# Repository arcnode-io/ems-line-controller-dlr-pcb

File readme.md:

# DLR PCB 🌡️⚡

> Single-PCB CM4 carrier for a solar-powered, cellular-connected RTU — mounts to a transmission tower cross-arm, integrates SoM + cellular modem + IEEE 738 sensor suite + solar/LiFePO4 power management. Feeds [`dlr-operating-envelope`](https://gitlab.com/arcnode-io/dlr-operating-envelope).

Solar-powered remote terminal unit (RTU) deployed unattended on transmission tower cross-arms. A ~20W solar panel and ~50Wh LiFePO4 battery keep the CM4 running indefinitely with cellular PSM idle. A soldered Quectel BG770A (LTE Cat-M1) publishes sensor data and dynamic ratings to the MQTT broker — no site WiFi or wired backhaul required. The unit is designed for 30-year conductor-adjacent deployment with no scheduled maintenance.

~100x80mm 4-layer industrial carrier. Raspberry Pi CM4 (DF40 dual-connector) + Quectel BG770A LCC + FLIR Lepton 3.5 (SPI) + DHT22 (GPIO) + SI1145 (I2C) + YL-83 (analog via ADS1115). MPPT charger from PV input, LiFePO4 BMS, buck for 5V SoM rail, AP2112K LDO for 3.3V analog front-end. Conformal coated, IP55 when potted in field enclosure.

## System Context

```plantuml
rectangle transmission_tower {
  rectangle field_enclosure {
    rectangle dlr_carrier {
      rectangle cm4_som
      rectangle cellular_module
      rectangle sensors
      rectangle power_mgmt
    }
  }
  rectangle solar_panel
  rectangle lifepo4_battery
  rectangle conductor
}

queue mqtt_broker
rectangle dlr_pst_sim

solar_panel -d- power_mgmt: PV input
power_mgmt -l- lifepo4_battery: charge / discharge
power_mgmt -d- cm4_som: 5V / 3V3
conductor -u- sensors: thermal view\n(FLIR Lepton)
sensors -r- cm4_som: SPI / I2C / GPIO
cm4_som -r- cellular_module: UART + USB2
cellular_module -r- mqtt_broker: LTE Cat-M1
mqtt_broker -r- dlr_pst_sim: tap \n adjustment \n commands
```

The carrier is the physical sensing + edge-compute layer of the DLR feedback loop. Every measurement flows through the IEEE 738 calculation in [`dlr-operating-envelope`](https://gitlab.com/arcnode-io/dlr-operating-envelope) and ultimately determines whether the phase shift transformer adjusts its tap position.

## Board Spec

```mermaid
graph LR
    SOLAR["Solar Panel<br/>~20W 12V"] --> MPPT["MPPT Charger"]
    MPPT --> BAT["LiFePO4 4S<br/>~50Wh + BMS"]
    BAT --> BUCK["Buck<br/>5V 3A"]
    BUCK --> CM4["CM4 SoM<br/>DF40 x2"]
    BUCK --> BG["Quectel BG770A<br/>Cat-M1 LCC"]
    BUCK --> LDO["AP2112K<br/>3.3V LDO"]
    LDO --> ADC["ADS1115<br/>I2C 0x48"]
    LDO --> UV["SI1145<br/>I2C 0x60"]
    CM4 --> FLIR["FLIR Lepton 3.5<br/>SPI0 + GPIO25"]
    CM4 --> DHT["DHT22<br/>GPIO4"]
    CM4 --> ADC
    CM4 --> UV
    ADC --> RAIN["YL-83<br/>Analog 0-3.3V"]

    style SOLAR fill:#dc4,stroke:#333
    style MPPT fill:#a94,stroke:#333
    style BAT fill:#a94,stroke:#333
    style BUCK fill:#a94,stroke:#333
    style LDO fill:#a94,stroke:#333
    style CM4 fill:#4a9,stroke:#333,color:#fff
    style BG fill:#49a,stroke:#333,color:#fff
    style FLIR fill:#49a,stroke:#333,color:#fff
    style DHT fill:#94a,stroke:#333,color:#fff
    style ADC fill:#94a,stroke:#333,color:#fff
    style UV fill:#94a,stroke:#333,color:#fff
    style RAIN fill:#669,stroke:#333,color:#fff
```

## CM4 Pinout

```mermaid
flowchart LR
classDef default fill:transparent,stroke:#333
classDef pwr fill:#4a9,stroke:#333,color:#fff
classDef spi fill:#49a,stroke:#333,color:#fff
classDef i2c fill:#94a,stroke:#333,color:#fff
classDef gpio fill:#a94,stroke:#333,color:#fff
classDef uart fill:#a49,stroke:#333,color:#fff
classDef usb fill:#669,stroke:#333,color:#fff

subgraph cm4 ["CM4 (DF40-100)"]
  p_5v["5V_IN"]
  p_sda["GPIO2 SDA1"]
  p_scl["GPIO3 SCL1"]
  p_g4["GPIO4"]
  p_g25["GPIO25"]
  p_mosi["GPIO10 MOSI"]
  p_miso["GPIO9 MISO"]
  p_sck["GPIO11 SCLK"]
  p_ce0["GPIO8 CE0"]
  p_txd["GPIO14 TXD"]
  p_rxd["GPIO15 RXD"]
  p_usb["USB2 D+/D-"]
end

subgraph onboard ["Carrier Components"]
  flir["FLIR Lepton 3.5"]
  dht["DHT22"]
  si["SI1145"]
  ads["ADS1115"]
  yl["YL-83"]
  bg["BG770A"]
end

p_mosi --> flir
p_miso --> flir
p_sck --> flir
p_ce0 --> flir
p_g25 --> flir
p_g4 --> dht
p_sda --> si
p_scl --> si
p_sda --> ads
p_scl --> ads
ads --> yl
p_txd --> bg
p_rxd --> bg
p_usb --> bg

class p_5v pwr
class p_mosi,p_miso,p_sck,p_ce0 spi
class p_sda,p_scl i2c
class p_g4,p_g25 gpio
class p_txd,p_rxd uart
class p_usb usb
```

## Sensor Interfaces

| Sensor | Interface | CM4 Pins | Sample Rate | Measurement | Feeds IEEE 738 Variable |
|--------|-----------|----------|-------------|-------------|------------------------|
| FLIR Lepton 3.5 | SPI0 + VSYNC | GPIO 8, 9, 10, 11, 25 | 8.6 Hz (frame) | Conductor surface temp | $R_{thermal}$ |
| DHT22 | GPIO4 (1-Wire) | GPIO 4 | 0.5 Hz | Ambient temp + humidity | $T_{amb}$ |
| SI1145 | I2C (0x60) | GPIO 2, 3 | 10 Hz | UV / Visible / IR irradiance | $\Delta T_{solar}$ |
| YL-83 → ADS1115 | I2C (0x48) ch0 | GPIO 2, 3 | 860 SPS | Rain intensity (0–3.3V analog) | $\Delta T_{rain}$ |

Every sensor reading on this board maps to exactly one term in the IEEE 738 dynamic rating equation:

$$ I_{max} = \sqrt{\frac{q_c + q_r - q_s}{R_{ac}}} $$

## Anemometer Variants

Single PCB + single firmware binary. Variant lives in the **kit BOM** — sensor,
cable harness, PV panel, and battery differ per SKU. Both sensors speak
NMEA 0183 (`$..MWV`) over RS-485, so the firmware driver is talker-agnostic.

### Kit BOM

| Component | High-wind kit (`DLR-CRN-HW`) | Low-wind kit (`DLR-CRN-LW`) |
|-----------|------------------------------|------------------------------|
| PCB | `dlr-pcb-v1` (same) | `dlr-pcb-v1` (same) |
| Firmware | `dlr-operating-envelope` (same binary) | `dlr-operating-envelope` (same binary) |
| Sensor | Calypso ULP STD | Vaisala WMT702 |
| Sensor wire protocol | NMEA `$IIMWV` over RS-485 | NMEA `$WIMWV` over RS-485 |
| Sensor accuracy (V<2 m/s) | ±5 % + 0.2 m/s offset (1 m/s threshold) | **±0.1 m/s** (0.01 m/s threshold) |
| Sensor op temp | unspecified (consumer-grade) | -10 to +60 °C |
| Cable harness | 5 m bare-wire to M12-5P | 5 m Cannon Trident 19-way to M12-5P |
| PV panel | 20 W | **30 W** |
| Battery | 50 Wh LiFePO4 | **100 Wh LiFePO4** |
| Sticker | `HW-1.0` | `LW-1.0` |
| Kit cost (approx) | ~$650 | ~$2350 |

### When to deploy which variant

Per-site SKU pick uses NREL WIND Toolkit climatology (or customer SCADA wx
history when available). Threshold: fraction-of-year with V_w < 1 m/s
perpendicular to conductor.

| Climatology | Variant | Why |
|---|---|---|
| ≤ 15 % yr V_w < 1 m/s (ridge / coastal / open plain w/ mean ≥ 6 m/s) | high-wind | uplift slice below 1 m/s is marginal; static fallback below threshold is fine |
| > 15 % yr V_w < 1 m/s (valley / sheltered / open plain w/ mean ≤ 5 m/s) | low-wind | uplift slice is material; pay $1.7 k premium to capture it |

### Fallback policy (both variants)

When the sensor reports `void` status, times out, or has a checksum/parse
error, the driver returns `None`. The IEEE 738 layer collapses None →
`V_w = 0.0` → natural-convection-only ampacity = the conductor's static
rating. Same conservative fallback used for the icing-fallback policy.

### Variant power budget

| | High-wind | Low-wind |
|---|---|---|
| Sensor continuous draw | 1 mW | 480 mW |
| System daily energy | 29.1 Wh | 40.6 Wh |
| Winter PV harvest (worst) | 45 Wh | 67.5 Wh |
| Winter margin | 1.55× | **1.66×** |
| Battery autonomy at 0 PV | 1.58 d | **2.22 d** |

Low-wind variant's 30 W / 100 Wh upgrade absorbs the WMT702's higher draw and
restores both winter margin and 2-day autonomy.

## Power Budget

| Rail | Source | Consumer | Idle (PSM) | Typical | Peak |
|------|--------|----------|------------|---------|------|
| 5V | Buck | CM4 | 80 mA | 1400 mA | 3000 mA (boot) |
| 5V | Buck | Quectel BG770A | <1 mA | 100 mA | 250 mA (TX) |
| 5V | Buck | FLIR Lepton 3.5 | 150 mA | 150 mA | 650 mA (shutter) |
| 5V | Buck | DHT22 | 1.5 mA | 1.5 mA | 2.5 mA |
| 3.3V | AP2112K LDO | ADS1115 + SI1145 + YL-83 | 9 mA | 9 mA | 14 mA |
| | | **Total @ 5V equiv** | **240 mA** | **1660 mA** | **3920 mA** |

Daily energy with realistic CM4-always-on idle + 1/min sensor wake + 1/15 min cellular TX: **~29 Wh/day** (derived in `theory.ipynb`). A 50 Wh battery (90% DoD) gives ~1.6 days autonomy with no PV. A 20W panel at 2.5 sun-hours/day (winter Northeast US worst case) delivers ~45 Wh/day after MPPT η — **1.55x winter margin**, 2.5x annual avg.

## Environmental

| Parameter | Spec | Notes |
|-----------|------|-------|
| Operating temp | -20°C to +85°C | CM4 commercial spec; cold-start heater required below -20°C |
| Conformal coat | Dow Corning 1-2577 | Applied post-assembly, mask connectors |
| Enclosure rating | IP55 (with field enclosure) | Board alone is not rated |
| Vibration | IEC 60068-2-6 (5–500 Hz, 2g) | Transmission tower wind loading |
| Expected service life | 30 years | Matches conductor replacement cycle |
| MTBF | >200,000 hours | Derated per MIL-HDBK-217F |
| Mounting | M3 standoffs, 4-corner | Single rigid PCB — no stack |

## Fabrication Pipeline

The project fabricates **two PCBs** (per ADR-013): the main carrier and the Lepton daughterboard. Both go through the same flow.

```
 1. uv run poe notebook         → theory.ipynb: power budget + signal integrity
 2. uv run poe build            → SKiDL netlist (main carrier + daughterboard)
 3. uv run poe sim              → validate buck regulation, MPPT, I2C/SPI timing
 4. /generate-schematic         → professional .kicad_sch (each PCB)

    ┌──────────────────────────────────────────────────────┐
    │  HUMAN: open pcbnew, import netlist, save, close     │
    └──────────────────────────────────────────────────────┘

 5. /layout-pcb                 → place + autoroute + ground pour + DRC

    ┌──────────────────────────────────────────────────────┐
    │  HUMAN: review SVG, adjust pcb_placement.yaml        │
    └──────────────────────────────────────────────────────┘

 6. uv run poe validate-asm     → DRC 0 errors
 7. uv run poe generate-asm     → gerbers + BOM + CPL (per board)
```

## Layer Stack

| Layer | Use |
|-------|-----|
| F.Cu | Signal — high-speed (SPI 20MHz, USB2.0 to BG770A) |
| In1.Cu | GND pour (unbroken under FLIR + cellular module) |
| In2.Cu | Power planes — 5V, 3V3, BAT |
| B.Cu | Signal — low-speed (I2C, GPIO, UART) |

Unbroken ground plane under the Lepton is critical — SPI runs at 20 MHz and the thermal imager is noise-sensitive. USB2.0 to the BG770A is differential-routed at 90Ω matched impedance with GND directly below. Analog traces from YL-83 to ADS1115 are guard-ringed on F.Cu. Cellular antenna is 50Ω microstrip to a u.FL connector.

## Project Structure

```
├── pyproject.toml              # Dependencies and build config
├── theory.ipynb                # Power budget + signal integrity derivation
├── sim/
│   ├── model.py                # Buck regulation, LDO dropout, I2C/SPI timing
│   └── test_run.py             # Assert simulation matches theory
├── cad/
│   ├── netlist/
│   │   ├── model.py            # Top-level SKiDL circuit (main carrier)
│   │   ├── power.py            # MPPT + BMS + buck + LDO
│   │   ├── som.py              # CM4 DF40 connector + decoupling
│   │   ├── cellular.py         # BG770A + SIM holder + u.FL
│   │   ├── sensors.py          # FLIR (FFC), DHT22, SI1145, ADS1115, YL-83
│   │   ├── connectors.py       # Battery + debug + USB-C commissioning
│   │   └── lepton_daughter.py  # Daughterboard SKiDL (Molex socket + FFC)
│   ├── lepton_daughter/        # Second PCB (per ADR-013) — Lepton + bracket
│   ├── schematic/              # /generate-schematic output
│   ├── assembly/               # CadQuery → GLB pipeline (build_assembly.py)
│   ├── layout_spec.yaml        # Schematic block layout
│   ├── pcb_placement.yaml      # Main-PCB component positions
│   └── drawing-sheet.kicad_wks # Title block
├── output/
│   ├── drawings/               # Schematic SVG + PDF
│   ├── gerbers/                # Fabrication files
│   └── fab/                    # BOM + CPL for assembly
└── readme.md                   # This file
```

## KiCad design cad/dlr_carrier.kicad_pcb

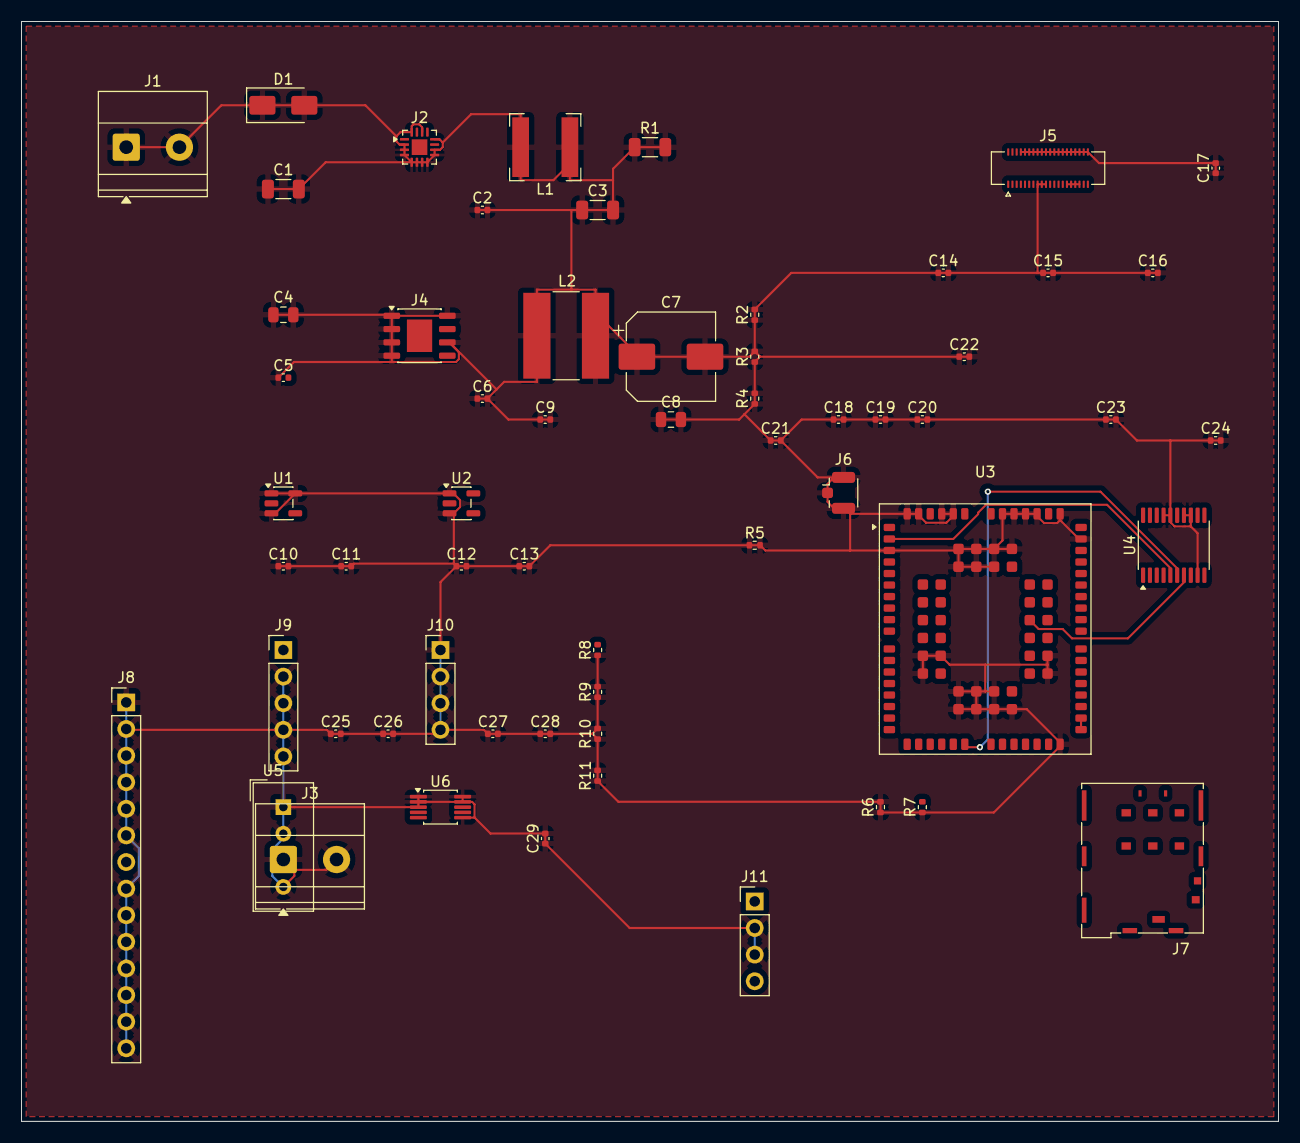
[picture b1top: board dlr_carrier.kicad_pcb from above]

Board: 2 copper layers, 120.0 x 105.0 mm, 60 parts (0 on the bottom side), 9 nets.

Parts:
C1, C3: 22uF; C_1206_3216Metric
C2, C5, C6, C9, C14, C15, C16, C17, C19, C20, C23, C24, C25, C26, C27, C28: 100nF; C_0402_1005Metric
C4: 4.7uF; C_0805_2012Metric
C7: 470uF; CP_Elec_8x10
C8: 22uF; C_0805_2012Metric
C10, C11, C12, C13: 1uF; C_0402_1005Metric
C18: 4.7uF; C_0402_1005Metric
C21, C22: DNP; C_0402_1005Metric
C29: 10nF; C_0402_1005Metric
D1: SS34; D_SMA
J1: PV_IN; TerminalBlock_Phoenix_MKDS-1,5-2-5.08_1x02_P5.08mm_Horizont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
J2: BQ24650; HVQFN-16-1EP_3x3mm_P0.5mm_EP1.5x1.5mm
J3: BAT; TerminalBlock_Phoenix_MKDS-1,5-2-5.08_1x02_P5.08mm_Horizont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
J4: LMR33630ADDA; HSOP-8-1EP_3.9x4.9mm_P1.27mm_EP2.41x3.1mm
J5: CM4_J2; Hirose_DF40HC(3.0)-40DS-0.4V_2x20_P0.4mm
J6: U.FL; U.FL_Hirose_U.FL-R-SMT-1_Vertical
J7: SIM; microSIM_JAE_SF53S006VCBR2000
J8: FLIR_LEPTON; PinHeader_1x14_P2.54mm_Vertical
J9: SI1145; PinHeader_1x05_P2.54mm_Vertical
J10: YL-83; PinHeader_1x04_P2.54mm_Vertical
J11: DEBUG_UART; PinHeader_1x04_P2.54mm_Vertical
L1: 6.8uH; L_Bourns-SRN6028
L2: 10uH; L_Bourns-SRN8040_8x8.15mm
R1: 20m; R_1206_3216Metric
R2: 39.2k; R_0402_1005Metric
R3, R7, R8, R9: 10k; R_0402_1005Metric
R4: 47k; R_0402_1005Metric
R5: 0R; R_0402_1005Metric
R6: 100k; R_0402_1005Metric
R10, R11: 2.2k; R_0402_1005Metric
U1: AP2112K-3.3; SOT-23-5
U2: LP5907MFX-3.8; SOT-23-5
U3: BG770A-NA; Quectel_BG95
U4: TXS0108E; TSSOP-20_4.4x6.5mm_P0.65mm
U5: DHT22; Aosong_DHT11_5.5x12.0_P2.54mm
U6: ADS1115; MSOP-10_3x3mm_P0.5mm

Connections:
+3V3: C1.1, C1.2, C2.1, C2.2, C3.1, C3.2, C4.1, C4.2, C5.1, C6.1, C6.2, C7.1, C7.2, C8.1, C8.2, C9.1, C9.2, C10.1, C10.2, C11.1, C11.2, C12.1, C12.2, C13.1, C13.2, C14.1, C14.2, C15.1, C15.2, C16.1, C16.2, C17.1, C17.2, C18.1, C18.2, C19.1, C19.2, C20.1, C20.2, C21.1, C21.2, C22.1, C22.2, C23.1, C23.2, C24.1, C24.2, C25.1, C25.2, C26.1, C26.2, C27.1, C27.2, C28.1, C28.2, C29.1, C29.2, D1.1 (K), D1.2 (A), J1.1, J1.2, J2.2, J2.3, J2.4, J2.5, J2.6, J2.7, J2.8, J2.9, J2.10, J2.12, J2.14, J2.16, J3.1, J3.2, J4.1, J4.2, J4.3, J4.4, J4.6, J4.8, J5.1, J5.3, J5.6, J5.8, J5.9, J5.10, J5.12, J5.13, J5.14, J5.15, J5.16, J5.17, J5.18, J5.19, J5.20, J5.21, J5.22, J5.24, J5.26, J5.27, J5.28, J5.29, J5.30, J5.31, J5.32, J5.33, J5.34, J5.35, J5.36, J5.37, J5.38, J5.40, J6.1 (In), J6.2 (Ext), J8.1, J8.2, J8.3, J8.4, J8.5, J8.6, J8.8, J8.9, J8.10, J8.11, J8.12, J8.13, J8.14, J9.2, J9.3, J9.4, J9.5, J10.1, J10.2, J10.3, J10.4, J11.2, J11.3, L1.1, L1.2, L2.1, L2.2, R1.1, R1.2, R2.1, R2.2, R3.1, R3.2, R4.1, R4.2, R5.1, R5.2, R6.1, R6.2, R7.1, R8.1, R9.1, R9.2, R10.1, R10.2, R11.1, R11.2, U1.1 (VIN), U1.3 (EN), U1.5 (VOUT), U2.1 (IN), U2.3 (EN), U3.3 (GND), U3.31 (GND), U3.48 (GND), U3.50 (GND), U3.52 (VBAT_RF), U3.53 (VBAT_RF), U3.54 (GND), U3.55 (GND), U3.58 (GND), U3.59 (GND), U3.61 (GND), U3.62 (GND), U3.67 (GND), U3.68 (GND), U3.69 (GND), U3.70 (GND), U3.71 (GND), U3.72 (GND), U3.73 (GND), U3.74 (GND), U3.79 (GND), U3.80 (GND), U3.81 (GND), U3.82 (GND), U3.87 (GPIO20), U3.89 (GND), U3.90 (GND), U3.91 (GND), U3.100 (GND), U3.101 (GND), U3.102 (GND), U4.9 (A8), U4.13 (B7), U4.14 (B6), U4.16 (B4), U4.17 (B3), U5.1 (VDD), U5.2 (DATA), U5.4 (GND), U6.1 (ADDR), U6.2 (ALERT/RDY), U6.3 (GND), U6.6 (AIN2), U6.9 (SDA), U6.10 (SCL)
/CELL_NET_STATUS: J5.25, U4.18 (B2)
/CELL_PWRKEY: J5.23, U4.15 (B5)
/CELL_PWRKEY_1V8: U3.24 (ADC0), U4.6 (A5)
/CELL_RESET_1V8: U3.2 (ADC1), U4.5 (A4)
/CELL_RX_1V8: U3.96 (PON_TRIG), U4.7 (A6)
/CELL_STATUS_1V8: U3.75 (USB_BOOT), U4.4 (A3)
/DBG_RX: J5.5, J11.1
unnamed: U3.32 (VBAT_BB), U3.33 (VBAT_BB)

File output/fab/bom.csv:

"Designator","Comment","Footprint","Quantity"
"C1,C3","22uF","Capacitor_SMD:C_1206_3216Metric","2"
"C2,C5,C6,C9,C14-C17,C19,C20,C23-C28","100nF","Capacitor_SMD:C_0402_1005Metric","16"
"C4","4.7uF","Capacitor_SMD:C_0805_2012Metric","1"
"C7","470uF","Capacitor_SMD:CP_Elec_8x10","1"
"C8","22uF","Capacitor_SMD:C_0805_2012Metric","1"
"C10-C13","1uF","Capacitor_SMD:C_0402_1005Metric","4"
"C18","4.7uF","Capacitor_SMD:C_0402_1005Metric","1"
"C21,C22","DNP","Capacitor_SMD:C_0402_1005Metric","2"
"C29","10nF","Capacitor_SMD:C_0402_1005Metric","1"
"D1","SS34","Diode_SMD:D_SMA","1"
"J1","PV_IN","TerminalBlock_Phoenix:TerminalBlock_Phoenix_MKDS-1,5-2-5.08_1x02_P5.08mm_Horizontal","1"
"J2","BQ24650","Package_DFN_QFN:HVQFN-16-1EP_3x3mm_P0.5mm_EP1.5x1.5mm","1"
"J3","BAT","TerminalBlock_Phoenix:TerminalBlock_Phoenix_MKDS-1,5-2-5.08_1x02_P5.08mm_Horizontal","1"
"J4","LMR33630ADDA","Package_SO:HSOP-8-1EP_3.9x4.9mm_P1.27mm_EP2.41x3.1mm","1"
"J5","CM4_J2","Connector_Hirose_DF40:Hirose_DF40HC(3.0)-40DS-0.4V_2x20_P0.4mm","1"
"J6","U.FL","Connector_Coaxial:U.FL_Hirose_U.FL-R-SMT-1_Vertical","1"
"J7","SIM","Connector_Card:microSIM_JAE_SF53S006VCBR2000","1"
"J8","FLIR_LEPTON","Connector_PinHeader_2.54mm:PinHeader_1x14_P2.54mm_Vertical","1"
"J9","SI1145","Connector_PinHeader_2.54mm:PinHeader_1x05_P2.54mm_Vertical","1"
"J10","YL-83","Connector_PinHeader_2.54mm:PinHeader_1x04_P2.54mm_Vertical","1"
"J11","DEBUG_UART","Connector_PinHeader_2.54mm:PinHeader_1x04_P2.54mm_Vertical","1"
"L1","6.8uH","Inductor_SMD:L_Bourns-SRN6028","1"
"L2","10uH","Inductor_SMD:L_Bourns-SRN8040_8x8.15mm","1"
"R1","20m","Resistor_SMD:R_1206_3216Metric","1"
"R2","39.2k","Resistor_SMD:R_0402_1005Metric","1"
"R3,R7-R9","10k","Resistor_SMD:R_0402_1005Metric","4"
"R4","47k","Resistor_SMD:R_0402_1005Metric","1"
"R5","0R","Resistor_SMD:R_0402_1005Metric","1"
"R6","100k","Resistor_SMD:R_0402_1005Metric","1"
"R10,R11","2.2k","Resistor_SMD:R_0402_1005Metric","2"
"U1","AP2112K-3.3","Package_TO_SOT_SMD:SOT-23-5","1"
"U2","LP5907MFX-3.8","Package_TO_SOT_SMD:SOT-23-5","1"
"U3","BG770A-NA","RF_GSM:Quectel_BG95","1"
"U4","TXS0108E","Package_SO:TSSOP-20_4.4x6.5mm_P0.65mm","1"
"U5","DHT22","Sensor:Aosong_DHT11_5.5x12.0_P2.54mm","1"
"U6","ADS1115","Package_SO:MSOP-10_3x3mm_P0.5mm","1"

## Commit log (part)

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2026-04-10 init: readme + gitlab mirror job
2026-04-11 feat: scaffold from template
2026-04-12 📛 feat: add pipeline and coverage badges
2026-05-01 📝 docs: fix diagram arrow direction + label word-wrap
2026-05-14 chore: drop docs/superpowers/
2026-05-23 📝 docs(owners): add ems-iso to platform-engineer
2026-05-23 📝 docs(owners): rename ems-iso → platform-ems-iso (platform-generated, not internal to EMS)
